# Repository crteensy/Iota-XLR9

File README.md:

# Iota-XLR9
a small elrs receiver

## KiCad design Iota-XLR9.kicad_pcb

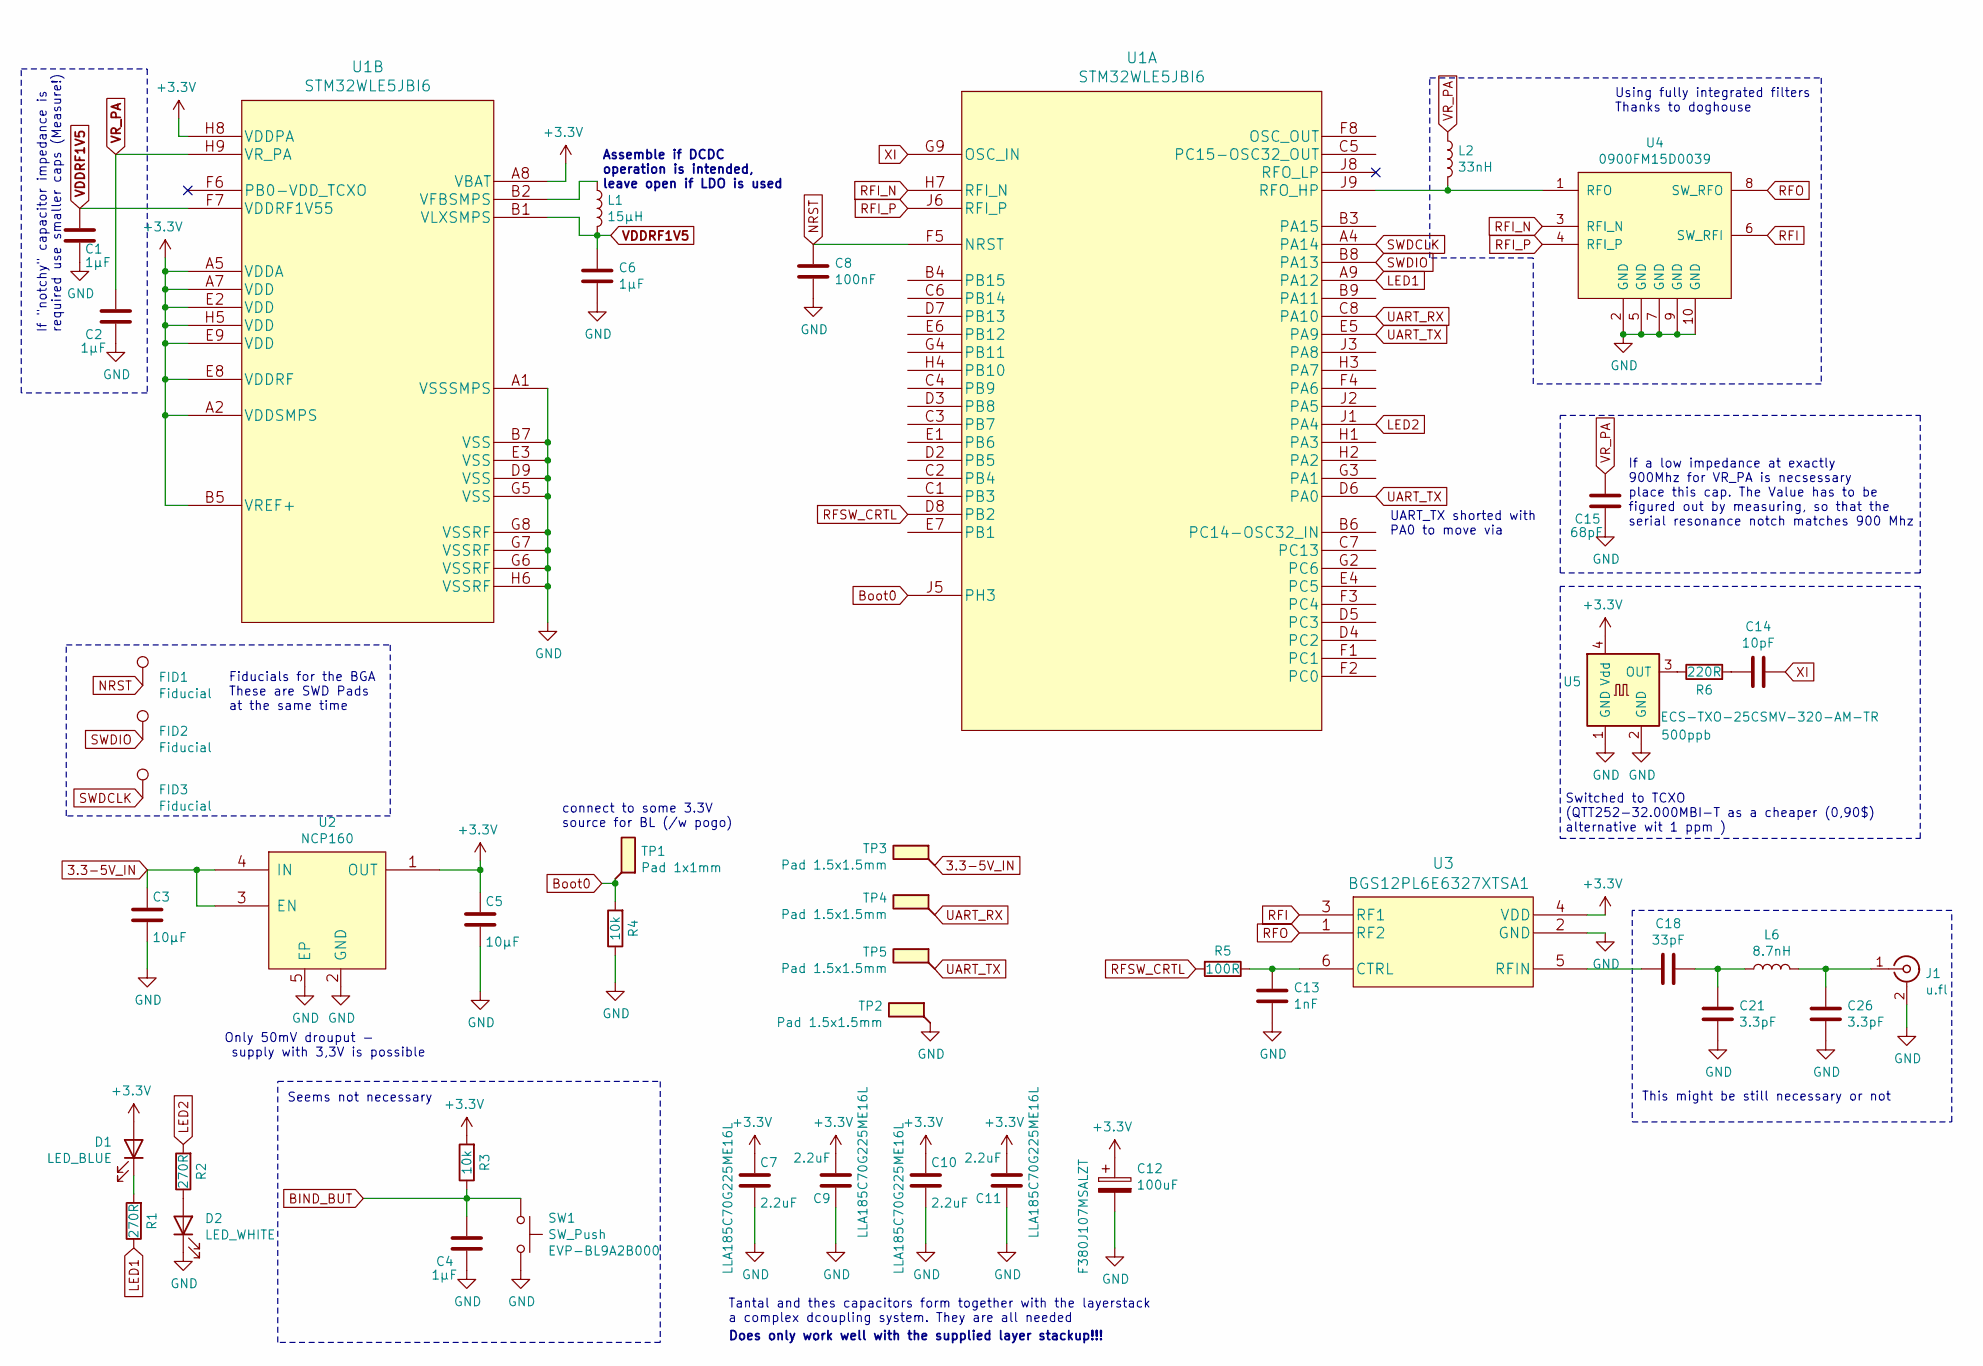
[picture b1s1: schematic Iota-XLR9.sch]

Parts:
C1, C2, C4, C6: 1µF; C_0201_0603Metric_dense
C3, C5: 10µF; L_0402_1005Metric_dense
C7, C9, C10, C11: 2.2uF; 0805_low_esl_cap_avx_w_via_dense
C8: 100nF; C_0201_0603Metric_dense
C12: 100uF; AVX_S_CASE
C13: 1nF; C_0201_0603Metric_dense
C14: 10pF; C_0201_0603Metric_dense
C15: 68pF; C_0201_0603Metric_dense
C18: 33pF; C_0201_0603Metric_dense
C21, C26: 3.3pF; C_0201_0603Metric_dense
D1: LED_BLUE; LED_0201_0603Metric
D2: LED_WHITE; LED_0201_0603Metric
FID1, FID2, FID3: Fiducial; Fiducial_0.5mm_Dia_1mm_Outer
J1: u.fl; U.FL_Molex_MCRF_73412-0110_Vertical
L1: 15µH; L_0603_1608Metric
L2: 33nH; R_0201_0603Metric_dense
L6: 8.7nH; L_0402_1005Metric_dense
R1, R2: 270R; R_0201_0603Metric_dense
R3, R4: 10k; R_0201_0603Metric_dense
R5: 100R; R_0201_0603Metric_dense
R6: 220R; R_0201_0603Metric_dense
SW1: SW_Push; EVPBL9A2B000
TP1: Pad 1x1mm; TestPoint_Pad_1.0x1.0mm
TP2, TP3, TP4, TP5: Pad 1.5x1.5mm; TestPoint_Pad_1.5x2mm
U1: STM32WLE5JBI6
U2: NCP160; UDFN-4_1x1mm_P0.65mm
U3: BGS12PL6E6327XTSA1
U4: 0900FM15D0039
U5: ECS-TXO-25CSMV-320-AM-TR; ECS-TXO-25CSMV-320-AM-TR_reduced_pads; Tolerance 500ppb

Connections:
3.3-5V_IN: C3.1, TP3.1, U2.3 (EN), U2.4 (IN)
+3V3: C5.1, C7.1, C9.2, C10.1, C11.2, C12.1, D1.2 (A), R3.2, U1.A2 (VDDSMPS), U1.A5 (VDDA), U1.A7 (VDD), U1.A8 (VBAT), U1.B5 (VREF+), U1.E2 (VDD), U1.E8 (VDDRF), U1.E9 (VDD), U1.H5 (VDD), U1.H8 (VDDPA), U2.1 (OUT), U3.4 (VDD), U5.4 (Vdd)
BIND_BUT: C4.1, R3.1, SW1.1
Boot0: R4.2, TP1.1, U1.J5 (PH3)
GND: C1.2, C2.2, C3.2, C4.2, C5.2, C6.2, C7.2, C8.2, C9.1, C10.2, C11.1, C12.2, C13.1, C15.2, C21.2, C26.2, D2.1 (K), J1.2 (Ext), R4.1, SW1.2, TP2.1, U1.A1 (VSSSMPS), U1.B7 (VSS), U1.D9 (VSS), U1.E3 (VSS), U1.G5 (VSS), U1.G6 (VSSRF), U1.G7 (VSSRF), U1.G8 (VSSRF), U1.H6 (VSSRF), U2.2 (GND), U2.5 (EP), U3.2 (GND), U4.2 (GND), U4.5 (GND), U4.7 (GND), U4.9 (GND), U4.10 (GND), U5.1 (GND), U5.2 (GND)
LED1: R1.1, U1.A9 (PA12)
LED2: R2.2, U1.J1 (PA4)
NRST: C8.1, FID1.1, U1.F5 (NRST)
unnamed: C13.2, R5.1, U3.6 (CTRL)
unnamed: C14.1, R6.2
unnamed: C18.1, U3.5 (RFIN)
unnamed: C18.2, C21.1, L6.1
unnamed: C26.1, J1.1 (In), L6.2
unnamed: D1.1 (K), R1.2
unnamed: D2.2 (A), R2.1
unnamed: L1.1, U1.B2 (VFBSMPS)
unnamed: L2.2, U1.J9 (RFO_HP), U4.1 (RFO)
unnamed: R6.1, U5.3 (OUT)
RFI: U3.3 (RF1), U4.6 (SW_RFI)
RFI_N: U1.H7 (RFI_N), U4.3 (RFI_N)
RFI_P: U1.J6 (RFI_P), U4.4 (RFI_P)
RFO: U3.1 (RF2), U4.8 (SW_RFO)
RFSW_CRTL: R5.2, U1.D8 (PB2)
SWDCLK: FID3.1, U1.A4 (PA14)
SWDIO: FID2.1, U1.B8 (PA13)
UART_RX: TP4.1, U1.C8 (PA10)
UART_TX: TP5.1, U1.D6 (PA0), U1.E5 (PA9)
VDDRF1V5: C1.1, C6.1, L1.2, U1.B1 (VLXSMPS), U1.F7 (VDDRF1V55)
VR_PA: C2.1, C15.1, L2.1, U1.H9 (VR_PA)
XI: C14.2, U1.G9 (OSC_IN)

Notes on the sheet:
Assemble if DCDC operation is intended, leave open if LDO is used
If "notchy" capacitor impedance is required use smaller caps (Measure!)
This might be still necessary or not
Only 50mV drouput - supply with 3,3V is possible
connect to some 3.3V source for BL (/w pogo)
Using fully integrated filters Thanks to doghouse
Switched to TCXO (QTT252-32.000MBI-T as a cheaper (0,90$) alternative wit 1 ppm )
Seems not necessary
Tantal and thes capacitors form together with the layerstack a complex dcoupling system. They are all needed
UART_TX shorted with PA0 to move via
Fiducials for the BGA These are SWD Pads at the same time
Does only work well with the supplied layer stackup!!!
If a low impedance at exactly 900Mhz for VR_PA is necsessary place this cap. The Value has to be figured out by measuring, so that the serial resonance notch matches 900 Mhz

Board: 4 copper layers, 44 parts (4 on the bottom side), 30 nets, no tracks yet.

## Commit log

2021-03-16 created sketch
